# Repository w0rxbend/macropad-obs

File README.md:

# macropad-obs

An OBS Studio control pad: a 3.5 inch display, a tall narrow strip display, 9 MX keys, 4 small
buttons and 3 push knobs on a flat milled slab. An ESP32-S3 joins Wi-Fi and is the obs-websocket 5
client itself; no PC process runs between the pad and OBS. A Linux Tauri app sets the pad up over
USB: OBS URL, SSID, secrets (write only), key mapping and display layout.

The contract is `docs/spec/spec-v2.md` with the owner's answers in `docs/spec/decisions-v2.md`. The
design as built is `docs/design.md`. The plan and task cards are `tasks/plan.md` and `tasks/todo.md`.

That picture is a mesh render of the style A case, cnc variant (`just cad render`); the keycaps are
envelope boxes. It is not a photograph. Nothing in it has been printed, assembled, or flashed.

## No hardware yet

No board, case or panel exists. Nothing has run on a chip. Every hardware number in this repo is a
datasheet value, an arithmetic result, or a MEASURE tag. What to buy, print, mill and assemble is
`docs/build-guide.md`. The bring-up order for the first board is `docs/bringup.md`.

## Commands

| Command | What it does |
| --- | --- |
| `just test` | gcc ASan/UBSan on `firmware/core`, cargo in `host/`, python3 checks, padsim end to end. No Docker, no window |
| `just padsim-smoke` | builds padsim (the core on the PC) and runs its smoke script |
| `just gate` | board-order gate: lists each open MEASURE on a gated `board.toml` entry; exits 1 while one is open. Not part of `just test` |
| `just firmware` | ESP-IDF v6.1.1 in Docker: builds the merged image `.build/esp32s3/macropad-obs-merged.bin` and checks the built partition table |
| `just flash` | writes that image over the ROM USB port with esptool in the IDF image. Needs the pad |
| `just pcb` | KiCad 9.0.9 in Docker: ERC, placement, critical copper, Freerouting, fab set, DRC. `just pcb step` exports the board STEP in KiCad 10.0.7-full |
| `just pcb-test-kicad` | the `pcb/gen` tests in the pinned KiCad image, where the pcbnew tests run |
| `just cad` | build123d in `cad/.venv`: case, exports with read-back, coupons, laser sheets, renders, fit against the board STEP |
| `just app` | `cargo build` of the Tauri app on the host. Needs `webkit2gtk-4.1` |
| `just app-check` | the same build in a Docker image made from the local `kicad/kicad:10.0.7`, then the window under Xvfb |

`cad/.venv` is local and gitignored. Create it with `uv` from `cad/pyproject.toml`.

## Status

Each row is a command run on this machine on 2026-11-20, with its real exit code. A gated command is
"not run: gated" and never counts as a pass.

| Command | Exit | What the run showed |
| --- | --- | --- |
| `just test` | 0 | `test-firmware`: 20 C test programs under ASan/UBSan. `test-host`: 135 cargo tests, clippy and fmt; padsim end to end for criteria 4, 4b, 4c, 5, 8, 9 and the app pages. `check`, `numbers` (13), `cad-check` (11) and `pcb-test` (218, 39 pcbnew tests skipped; they run in `just pcb-test-kicad`) |
| `just padsim-smoke` | 0 | a cut at program call 3, then the next start read the same NOR image |
| `just gate` | 1 | 18 open MEASURE tags on gated entries: no board order. Expected until the panels are calipered and the coupons printed |
| `just firmware` | 0 | image 1,040,608 bytes, DIRAM 93,058 bytes free; 5 partition rows match spec 10. Built only; never run on a chip |
| `just pcb-test-kicad` | 0 | 218 tests OK, 1 skipped, in `kicad/kicad:9.0.9` |
| `just pcb` | 0 | ERC clean; routed DRC at error severity: 0 violations, 0 unconnected, 0 parity, 4 copper layers; fab set byte-repeatable, 48 BOM findings listed. Provisional: J3 and J4 are `PLACEHOLDER_*` FPC footprints, so the set stays in ignored `pcb/.build/` |
| `just pcb step` | 0 | the STEP reads back 75 solids. Provisional, as above. Run it after `just pcb`: `just cad` fit exits 1 on a STEP older than the board |
| `just cad` | 0 | every step 0 problems; 42 case, 12 2D, 10 envelope, 3 laser, 12 B3F cap, 6 knob and 54 coupon files read back; FCStd not built (needs FreeCAD, not approved); fit: 0 interferences, DSA keycap seat not checked |
| `just app` | 0 | the Tauri shell and its 20 commands over `app_core` build on the host. The window was not opened here |
| `just app-check` | 0 | the same build in the image; the window showed under Xvfb within 10 s and was alive 5 s later. No look by eye (D6), no pad |
| `just flash` | not run: gated | no pad exists |

## Not built, not run, not proven

- **Not built:** the board (`just gate` exits 1), the printed case, the milled case, the FCStd, the
  committed fab set (task 5.12), the FPC footprints (task 5.3b), the dev kit spike firmware
  (task S.1).
- **Not run:** anything on an ESP32-S3, the panels, or a real OBS. The app pages (tasks 3.7, 3.8)
  ran only against padsim and under Xvfb: no real pad, no look by eye (D6), no real firmware
  update. No spike results (S.3), no dev kit acceptance (4.8), no bring-up (H.2), no JLCPCB or CNC
  quote (F.1, F.2).
- **Not proven without hardware:** Wi-Fi through the back-wall insert, reconnect times, input to
  scene change under 100 ms, strip update within 200 ms, redraw timing and SPI above 15 MHz, VBUS
  under 500 mA, the panel init tables, the ROM port after `BOOTLOADER`, no secret in the `nvs` and
  `cred` dumps or the UART log, case fit with no sanding. Each has a task card in `tasks/todo.md`
  (S.3, 4.8, H.2 to H.11).

VID `0x1209` PID `0x4F42` is not registered with pid.codes.

## udev

```text
sudo cp app/udev/70-macropad-obs.rules /etc/udev/rules.d/
sudo udevadm control --reload
sudo udevadm trigger
```

Two rules, both `TAG+="uaccess"`: the pad's CDC port, VID `1209` PID `4f42`, symlink `macropad-obs`;
and the ESP32-S3 ROM download port, VID `303a` PID `1001`. There is no `plugdev` group and no `MODE`.

## License

`LICENSE` is the MIT License for `firmware/`, `host/`, `app/`, and `tools/`.

https://opensource.org/license/mit

`LICENSE.cern-ohl-s` is CERN-OHL-S-2.0 for `pcb/` and `cad/`. Hardware sources are not MIT.

https://cern.ch/cern-ohl

## MEASURE and UNVERIFIED

Sizes that come from no datasheet stay MEASURE until a caliper, a sample or a print coupon gives
them. `just gate` lists the ones that block a board order. LCSC cells stay `UNVERIFIED`.

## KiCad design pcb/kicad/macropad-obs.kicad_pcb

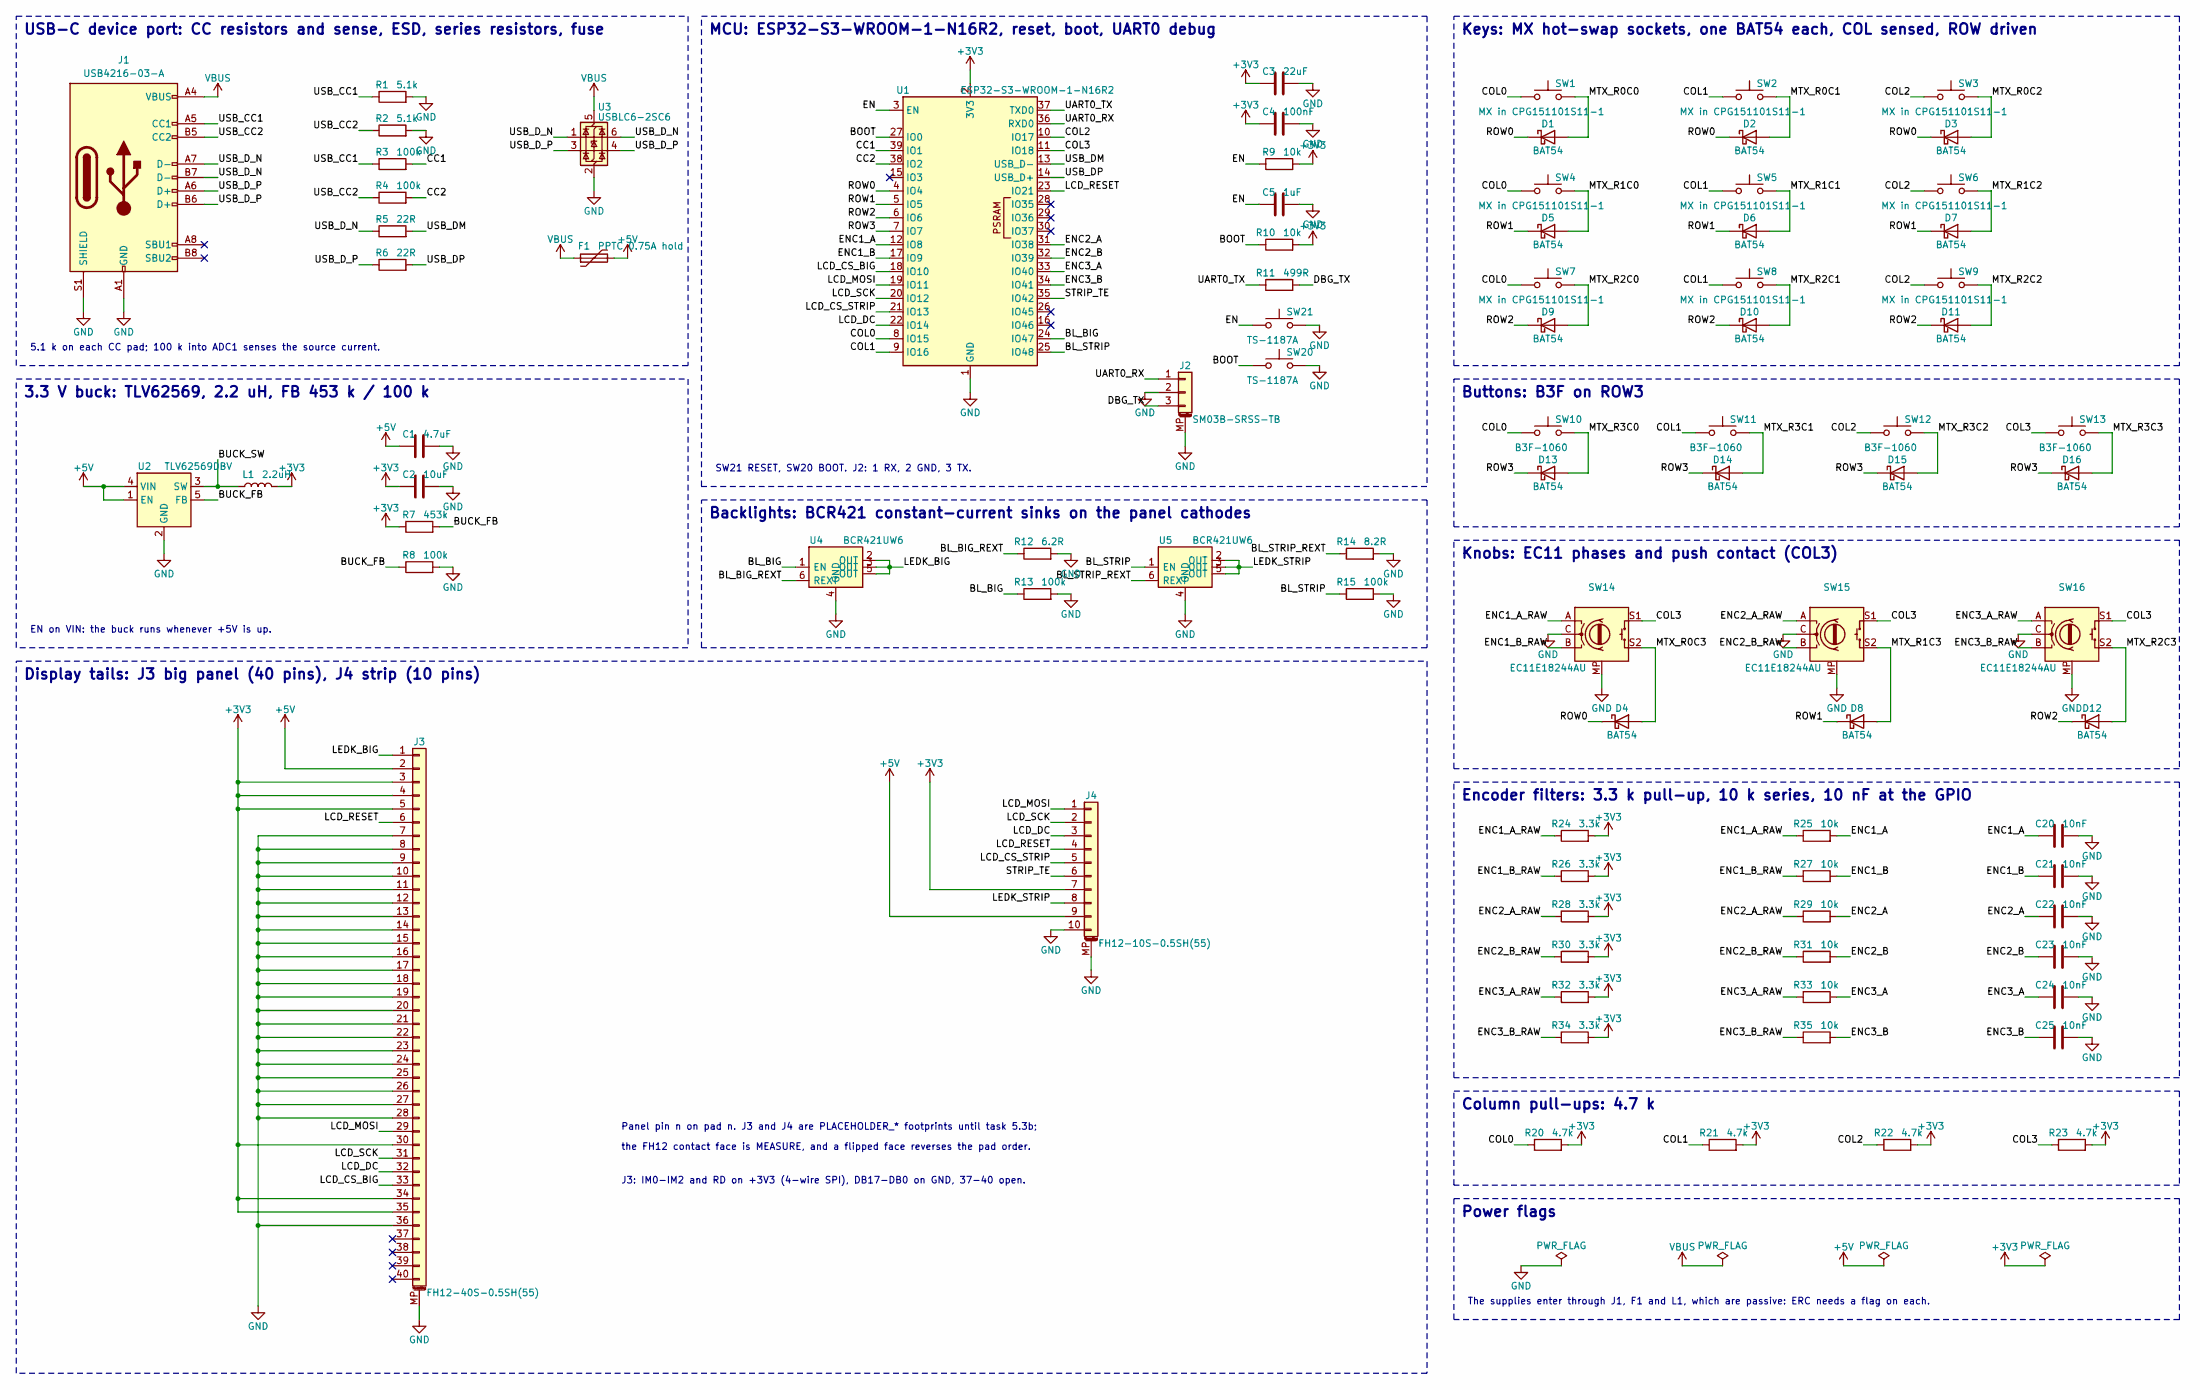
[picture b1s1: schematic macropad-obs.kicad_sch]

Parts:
C1: 4.7uF; C_0805_2012Metric; LCSC UNVERIFIED
C2: 10uF; C_0805_2012Metric; LCSC UNVERIFIED
C3: 22uF; C_0805_2012Metric; LCSC UNVERIFIED
C4: 100nF; C_0402_1005Metric; LCSC UNVERIFIED
C5: 1uF; C_0402_1005Metric; LCSC UNVERIFIED
C20, C21, C22, C23, C24, C25: 10nF; C_0402_1005Metric; LCSC UNVERIFIED
D1, D2, D3, D4, D5, D6, D7, D8, D9, D10, D11, D12, D13, D14, D15, D16: BAT54; D_SOD-123; LCSC UNVERIFIED
F1: PPTC 0.75A hold; Fuse_1206_3216Metric; LCSC UNVERIFIED
J1: USB4216-03-A; USB_C_Receptacle_GCT_USB4216-03-A; LCSC UNVERIFIED
J2: SM03B-SRSS-TB; JST_SH_SM03B-SRSS-TB_1x03-1MP_P1.00mm_Horizontal; LCSC UNVERIFIED
J3: FH12-40S-0.5SH(55); PLACEHOLDER_FPC_FH12-40S; LCSC UNVERIFIED
J4: FH12-10S-0.5SH(55); PLACEHOLDER_FPC_FH12-10S; LCSC UNVERIFIED
L1: 2.2uH; L_1008_2520Metric; LCSC UNVERIFIED
R1, R2: 5.1k; R_0402_1005Metric; LCSC UNVERIFIED
R3, R4, R8, R13, R15: 100k; R_0402_1005Metric; LCSC UNVERIFIED
R5, R6: 22R; R_0402_1005Metric; LCSC UNVERIFIED
R7: 453k; R_0402_1005Metric; LCSC UNVERIFIED
R9, R10, R25, R27, R29, R31, R33, R35: 10k; R_0402_1005Metric; LCSC UNVERIFIED
R11: 499R; R_0402_1005Metric; LCSC UNVERIFIED
R12: 6.2R; R_0805_2012Metric; LCSC UNVERIFIED
R14: 8.2R; R_0805_2012Metric; LCSC UNVERIFIED
R20, R21, R22, R23: 4.7k; R_0402_1005Metric; LCSC UNVERIFIED
R24, R26, R28, R30, R32, R34: 3.3k; R_0402_1005Metric; LCSC UNVERIFIED
SW1, SW2, SW3, SW4, SW5, SW6, SW7, SW8, SW9: MX in CPG151101S11-1; MX_Hotswap; LCSC UNVERIFIED
SW10, SW11, SW12, SW13: B3F-1060; SW_TH_Tactile_Omron_B3F-100x; LCSC UNVERIFIED
SW14, SW15, SW16: EC11E18244AU; RotaryEncoder_Alps_EC11E-Switch_Vertical_H20mm; LCSC UNVERIFIED
SW20, SW21: TS-1187A; SW_Push_1P1T_XKB_TS-1187A; LCSC UNVERIFIED
U1: ESP32-S3-WROOM-1-N16R2; ESP32-S3-WROOM-1; LCSC UNVERIFIED
U2: TLV62569DBV; SOT-23-5; LCSC UNVERIFIED
U3: USBLC6-2SC6; SOT-23-6; LCSC UNVERIFIED
U4, U5: BCR421UW6; SOT-23-6; LCSC UNVERIFIED

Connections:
+3V3: C2.1, C3.1, C4.1, J3.3, J3.4, J3.5, J3.30, J3.34, J3.35, J4.7, L1.2, R7.1, R9.2, R10.2, R20.2, R21.2, R22.2, R23.2, R24.2, R26.2, R28.2, R30.2, R32.2, R34.2, U1.2 (3V3)
+5V: C1.1, F1.2, J3.2, J4.9, U2.1 (EN), U2.4 (VIN)
/BL_BIG: R13.1, U1.24 (IO47), U4.1 (EN)
/BL_BIG_REXT: R12.1, U4.6 (REXT)
/BL_STRIP: R15.1, U1.25 (IO48), U5.1 (EN)
/BL_STRIP_REXT: R14.1, U5.6 (REXT)
/BOOT: R10.1, SW20.1, U1.27 (IO0)
/BUCK_FB: R7.2, R8.1, U2.5 (FB)
/BUCK_SW: L1.1, U2.3 (SW)
/CC1: R3.2, U1.39 (IO1)
/CC2: R4.2, U1.38 (IO2)
/COL0: R20.1, SW1.1, SW4.1, SW7.1, SW10.1, U1.8 (IO15)
/COL1: R21.1, SW2.1, SW5.1, SW8.1, SW11.1, U1.9 (IO16)
/COL2: R22.1, SW3.1, SW6.1, SW9.1, SW12.1, U1.10 (IO17)
/COL3: R23.1, SW13.1, SW14.S1, SW15.S1, SW16.S1, U1.11 (IO18)
/DBG_TX: J2.3, R11.2
/EN: C5.1, R9.1, SW21.1, U1.3 (EN)
/ENC1_A: C20.1, R25.2, U1.12 (IO8)
/ENC1_A_RAW: R24.1, R25.1, SW14.A
/ENC1_B: C21.1, R27.2, U1.17 (IO9)
/ENC1_B_RAW: R26.1, R27.1, SW14.B
/ENC2_A: C22.1, R29.2, U1.31 (IO38)
/ENC2_A_RAW: R28.1, R29.1, SW15.A
/ENC2_B: C23.1, R31.2, U1.32 (IO39)
/ENC2_B_RAW: R30.1, R31.1, SW15.B
/ENC3_A: C24.1, R33.2, U1.33 (IO40)
/ENC3_A_RAW: R32.1, R33.1, SW16.A
/ENC3_B: C25.1, R35.2, U1.34 (IO41)
/ENC3_B_RAW: R34.1, R35.1, SW16.B
/LCD_CS_BIG: J3.33, U1.18 (IO10)
/LCD_CS_STRIP: J4.5, U1.21 (IO13)
/LCD_DC: J3.32, J4.3, U1.22 (IO14)
/LCD_MOSI: J3.29, J4.1, U1.19 (IO11)
/LCD_RESET: J3.6, J4.4, U1.23 (IO21)
/LCD_SCK: J3.31, J4.2, U1.20 (IO12)
/LEDK_BIG: J3.1, U4.2 (OUT), U4.3 (OUT), U4.5 (OUT)
/LEDK_STRIP: J4.8, U5.2 (OUT), U5.3 (OUT), U5.5 (OUT)
/MTX_R0C0: D1.2 (A), SW1.2
/MTX_R0C1: D2.2 (A), SW2.2
/MTX_R0C2: D3.2 (A), SW3.2
/MTX_R0C3: D4.2 (A), SW14.S2
/MTX_R1C0: D5.2 (A), SW4.2
/MTX_R1C1: D6.2 (A), SW5.2
/MTX_R1C2: D7.2 (A), SW6.2
/MTX_R1C3: D8.2 (A), SW15.S2
/MTX_R2C0: D9.2 (A), SW7.2
/MTX_R2C1: D10.2 (A), SW8.2
/MTX_R2C2: D11.2 (A), SW9.2
/MTX_R2C3: D12.2 (A), SW16.S2
/MTX_R3C0: D13.2 (A), SW10.2
/MTX_R3C1: D14.2 (A), SW11.2
/MTX_R3C2: D15.2 (A), SW12.2
/MTX_R3C3: D16.2 (A), SW13.2
/ROW0: D1.1 (K), D2.1 (K), D3.1 (K), D4.1 (K), U1.4 (IO4)
/ROW1: D5.1 (K), D6.1 (K), D7.1 (K), D8.1 (K), U1.5 (IO5)
/ROW2: D9.1 (K), D10.1 (K), D11.1 (K), D12.1 (K), U1.6 (IO6)
/ROW3: D13.1 (K), D14.1 (K), D15.1 (K), D16.1 (K), U1.7 (IO7)
/STRIP_TE: J4.6, U1.35 (IO42)
/UART0_RX: J2.1, U1.36 (RXD0)
/UART0_TX: R11.1, U1.37 (TXD0)
/USB_CC1: J1.A5 (CC1), R1.1, R3.1
/USB_CC2: J1.B5 (CC2), R2.1, R4.1
/USB_DM: R5.2, U1.13 (USB_D-)
/USB_DP: R6.2, U1.14 (USB_D+)
/USB_D_N: J1.A7 (D-), J1.B7 (D-), R5.1, U3.1 (I/O1), U3.6 (I/O1)
/USB_D_P: J1.A6 (D+), J1.B6 (D+), R6.1, U3.3 (I/O2), U3.4 (I/O2)
GND: C1.2, C2.2, C3.2, C4.2, C5.2, C20.2, C21.2, C22.2, C23.2, C24.2, C25.2, J1.A1 (GND), J1.A12 (GND), J1.B1 (GND), J1.B12 (GND), J1.S1 (SHIELD), J2.2, J2.MP (MountPin), J3.7, J3.8, J3.9, J3.10, J3.11, J3.12, J3.13, J3.14, J3.15, J3.16, J3.17, J3.18, J3.19, J3.20, J3.21, J3.22, J3.23, J3.24, J3.25, J3.26, J3.27, J3.28, J3.36, J3.MP (MountPin), J4.10, J4.MP (MountPin), R1.2, R2.2, R8.2, R12.2, R13.2, R14.2, R15.2, SW14.C, SW14.MP, SW15.C, SW15.MP, SW16.C, SW16.MP, SW20.2, SW21.2, U1.1 (GND), U1.40 (GND), U1.41 (GND), U2.2 (GND), U3.2 (GND), U4.4 (GND), U5.4 (GND)
VBUS: F1.1, J1.A4 (VBUS), J1.A9 (VBUS), J1.B4 (VBUS), J1.B9 (VBUS), U3.5 (VBUS)

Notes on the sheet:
USB-C device port: CC resistors and sense, ESD, series resistors, fuse
5.1 k on each CC pad; 100 k into ADC1 senses the source current.
3.3 V buck: TLV62569, 2.2 uH, FB 453 k / 100 k
EN on VIN: the buck runs whenever +5V is up.
MCU: ESP32-S3-WROOM-1-N16R2, reset, boot, UART0 debug
SW21 RESET, SW20 BOOT. J2: 1 RX, 2 GND, 3 TX.
Backlights: BCR421 constant-current sinks on the panel cathodes
Keys: MX hot-swap sockets, one BAT54 each, COL sensed, ROW driven
Buttons: B3F on ROW3
Knobs: EC11 phases and push contact (COL3)
Encoder filters: 3.3 k pull-up, 10 k series, 10 nF at the GPIO
Column pull-ups: 4.7 k
Power flags
The supplies enter through J1, F1 and L1, which are passive: ERC needs a flag on each.
Display tails: J3 big panel (40 pins), J4 strip (10 pins)
Panel pin n on pad n. J3 and J4 are PLACEHOLDER_* footprints until task 5.3b;
the FH12 contact face is MEASURE, and a flipped face reverses the pad order.
J3: IM0-IM2 and RD on +3V3 (4-wire SPI), DB17-DB0 on GND, 37-40 open.

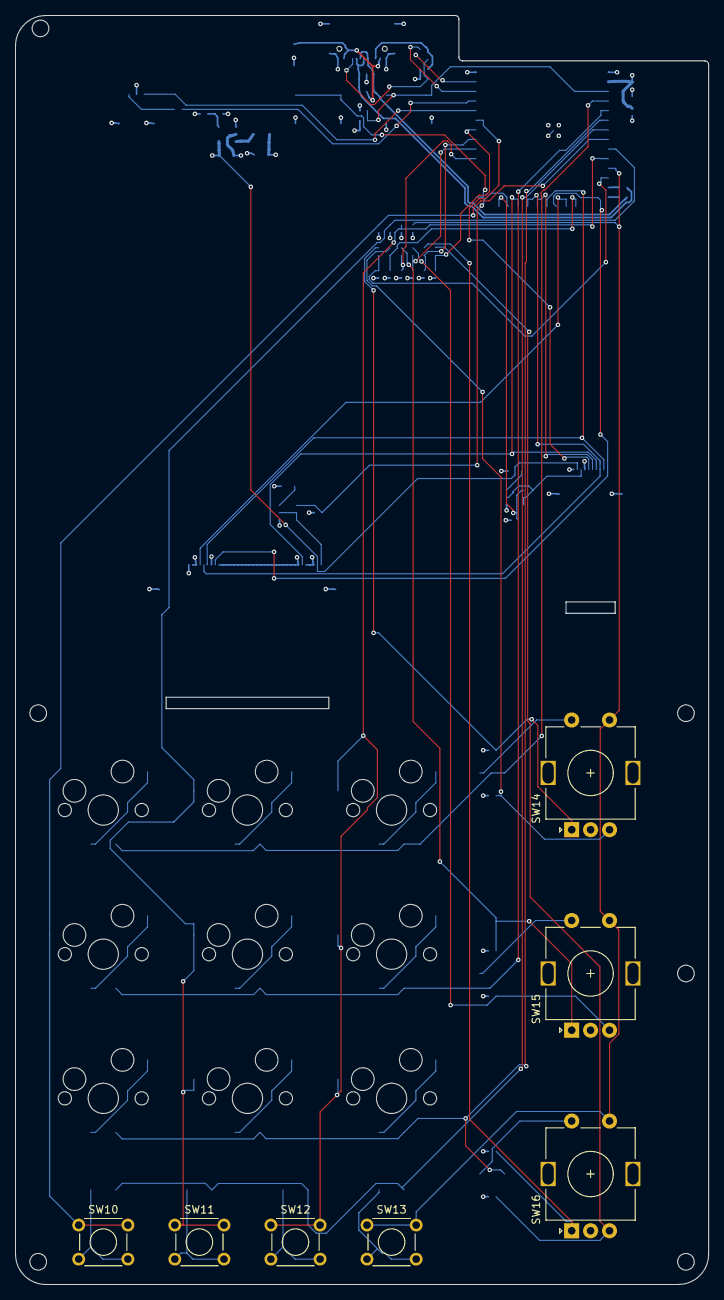
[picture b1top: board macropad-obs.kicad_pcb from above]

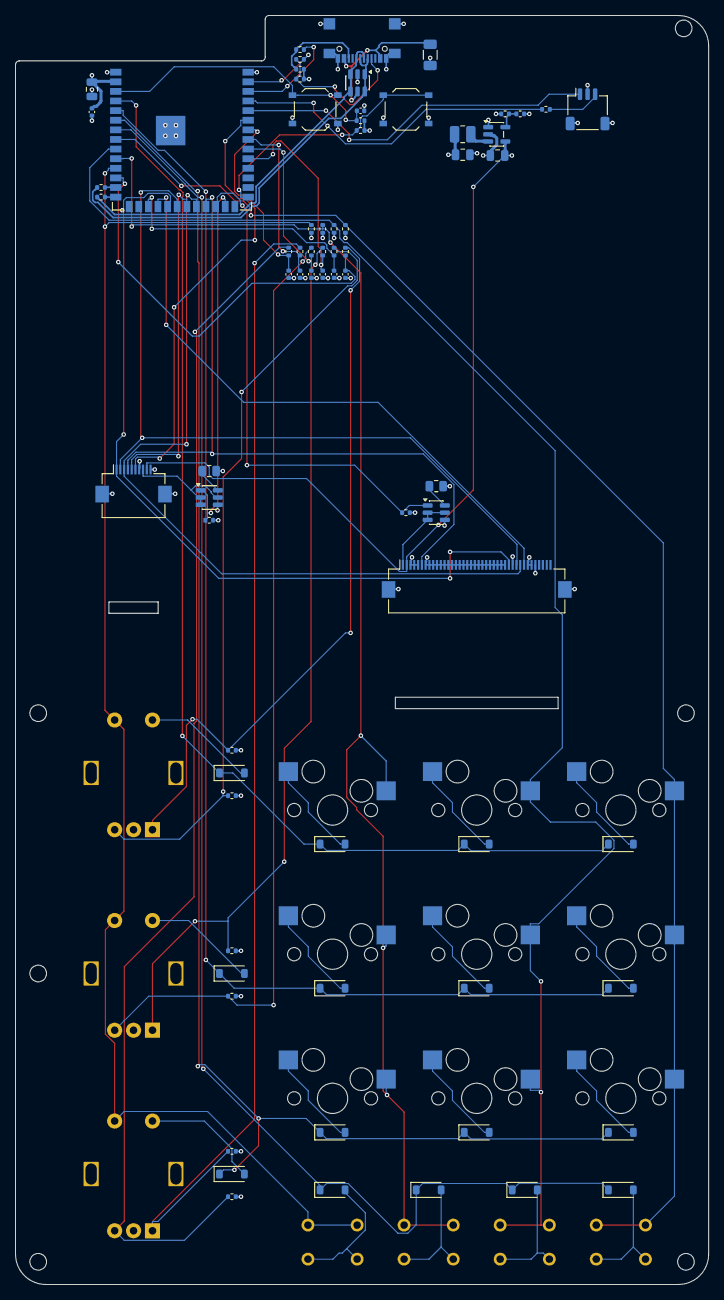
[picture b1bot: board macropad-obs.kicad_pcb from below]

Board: 4 copper layers, 91.6 x 167.7 mm, 93 parts (80 on the bottom side), 68 nets.

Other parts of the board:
H1, H2, H3, H4, H5, H6: M2; Hole_M2

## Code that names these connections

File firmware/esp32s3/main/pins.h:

// SPDX-License-Identifier: MIT
// GPIO map for macropad-obs on the ESP32-S3-WROOM-1-N16R2.
// Generated from board.toml by `python3 tools/check_pins.py --write`. Do not edit.
// IO3, IO45 and IO46 are strapping pins and stay open.
#pragma once

#define PIN_BOOT 0
#define PIN_CC1 1
#define PIN_CC2 2
#define PIN_ROW0 4
#define PIN_ROW1 5
#define PIN_ROW2 6
#define PIN_ROW3 7
#define PIN_ENC1_A 8
#define PIN_ENC1_B 9
#define PIN_LCD_CS_BIG 10
#define PIN_LCD_MOSI 11
#define PIN_LCD_SCK 12
#define PIN_LCD_CS_STRIP 13
#define PIN_LCD_DC 14
#define PIN_COL0 15
#define PIN_COL1 16
#define PIN_COL2 17
#define PIN_COL3 18
#define PIN_USB_DM 19
#define PIN_USB_DP 20
#define PIN_LCD_RESET 21
#define PIN_ENC2_A 38
#define PIN_ENC2_B 39
#define PIN_ENC3_A 40
#define PIN_ENC3_B 41
#define PIN_STRIP_TE 42
#define PIN_UART0_TX 43
#define PIN_UART0_RX 44
#define PIN_BL_BIG 47
#define PIN_BL_STRIP 48

// pid.codes PID is pending: not submitted yet.
#define USB_VID 0x1209
#define USB_PID 0x4F42

// Power cap, board.toml [power] (power.c). The backlight cap is MEASURE until S.3.
#define POWER_BACKLIGHT_CAP_PERMILLE 600
#define POWER_ENUMERATION_WAIT_MS 2000
#define POWER_CC_1A5_THRESHOLD_MV 746
